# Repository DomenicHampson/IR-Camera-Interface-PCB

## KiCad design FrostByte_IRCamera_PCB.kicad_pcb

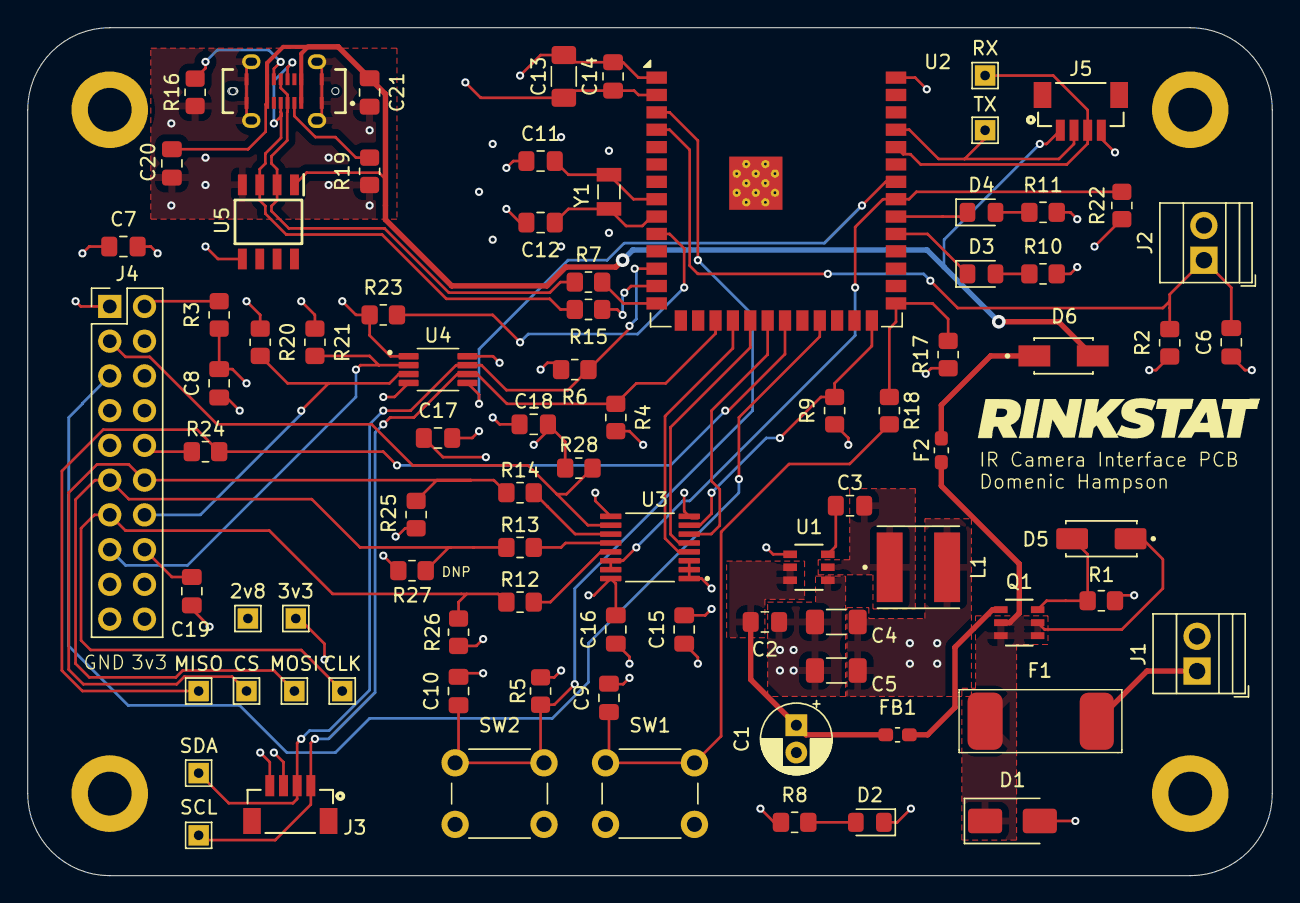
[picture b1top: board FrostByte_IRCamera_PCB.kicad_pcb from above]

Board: 4 copper layers, 91.0 x 62.0 mm, 88 parts (0 on the bottom side), 51 nets.

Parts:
2v8, 3v3: TestPoint; TestPoint_THTPad_1.5x1.5mm_Drill0.7mm
C1: 47uF; CP_Radial_D5.0mm_P2.00mm
C2: 2.2uF; C_0805_2012Metric_Pad1.18x1.45mm_HandSolder
C3, C6, C8, C9, C10, C14, C15, C16, C17, C18, C20, C21: 0.1uF; C_0805_2012Metric_Pad1.18x1.45mm_HandSolder
C4, C5: 22uF; C_1206_3216Metric_Pad1.33x1.80mm_HandSolder
C7, C19: 1uF; C_0805_2012Metric_Pad1.18x1.45mm_HandSolder
C11, C12: 8pF; C_0805_2012Metric_Pad1.18x1.45mm_HandSolder
C13: DNP; C_1206_3216Metric_Pad1.33x1.80mm_HandSolder
CLK: TestPoint; TestPoint_THTPad_1.5x1.5mm_Drill0.7mm
CS: TestPoint; TestPoint_THTPad_1.5x1.5mm_Drill0.7mm
D1: SMAJ33A; D_SMA
D2: LED_Red; LED_0805_2012Metric_Pad1.15x1.40mm_HandSolder
D3: LED_Blue; LED_0805_2012Metric_Pad1.15x1.40mm_HandSolder
D4: LED_Green; LED_0805_2012Metric_Pad1.15x1.40mm_HandSolder
D5: 15V; DIOM5226X240N
D6: B240A-13-F; DIOM5226X230N
F1: 3404.2413.11; Small_SMD_Fuse_Holder
F2: 1A Slow Blow; Fuse_0603_1608Metric_Pad1.05x0.95mm_HandSolder
FB1: PE-0603PFB121ST; C_0603_1608Metric_Pad1.08x0.95mm_HandSolder
H1, H2, H3, H4: MountingHole_Pad; MountingHole_3.2mm_M3_DIN965_Pad
J1: Power_Input; TerminalBlock_Xinya_XY308-2.54-2P_1x02_P2.54mm_Horizontal
J2: Conn_01x02_Socket; TerminalBlock_Xinya_XY308-2.54-2P_1x02_P2.54mm_Horizontal
J3: Conn_01x04_Socket; CONN4_BM04B-SRSS_JST
J4: Conn_02x10; PinHeader_2x10_P2.54mm_Vertical
J5: UART; CONN4_BM04B-SRSS_JST
J6: USB4120-03-C_REVA6; GCT_USB4120-03-C_REVA6
L1: 3.9uH; IND_VLS6045EX-6R8M
MISO: TestPoint; TestPoint_THTPad_1.5x1.5mm_Drill0.7mm
MOSI: TestPoint; TestPoint_THTPad_1.5x1.5mm_Drill0.7mm
Q1: SI3127DV-T1-GE3; TSOP-6L_VIS
R1: 100k; R_0805_2012Metric_Pad1.20x1.40mm_HandSolder
R2: 10k 1%; R_0805_2012Metric_Pad1.20x1.40mm_HandSolder
R3, R5, R9, R17, R22, R23, R25, R28: 10k; R_0805_2012Metric_Pad1.20x1.40mm_HandSolder
R4, R6, R20, R21: 2.2k; R_0805_2012Metric_Pad1.20x1.40mm_HandSolder
R7, R12, R13, R15, R24: 22; R_0805_2012Metric_Pad1.20x1.40mm_HandSolder
R8: 270; R_0805_2012Metric_Pad1.20x1.40mm_HandSolder
R10: 47; R_0805_2012Metric_Pad1.20x1.40mm_HandSolder
R11: 150; R_0805_2012Metric_Pad1.20x1.40mm_HandSolder
R14: 33; R_0805_2012Metric_Pad1.20x1.40mm_HandSolder
R16, R19: 5.1k; R_0805_2012Metric_Pad1.20x1.40mm_HandSolder
R18: 0; R_0805_2012Metric_Pad1.20x1.40mm_HandSolder
R26, R27: 47k; R_0805_2012Metric_Pad1.20x1.40mm_HandSolder
RX: TestPoint; TestPoint_THTPad_1.5x1.5mm_Drill0.7mm
SCL: TestPoint; TestPoint_THTPad_1.5x1.5mm_Drill0.7mm
SDA: TestPoint; TestPoint_THTPad_1.5x1.5mm_Drill0.7mm
SW1, SW2: SW_Push; SW_PUSH_6mm
TX: TestPoint; TestPoint_THTPad_1.5x1.5mm_Drill0.7mm
U1: AP63203WU-7; SOT-23-THIN-6_DDC_TEX
U2: ESP32-S3-WROOM-1
U3: SN74AXC4T245PWR; SOP65P640X120-16N
U4: TCA9517DGKR; SOP65P490X110-8N
U5: USB6B1RL; SOIC127P600X175-8N
Y1: 32.768kHz; XTAL_FC-135R_32.7680KA-AG0

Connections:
+2V8: 2v8.1, C8.1, C16.1, C18.2, C19.2, J4.16, R3.2, R20.1, R21.1, R23.2, R25.1, R26.1, R28.2, U3.16 (VCCB), U4.1 (VCCA)
+3.3V: 3v3.1, C4.1, C5.1, C7.1, C13.1, C14.1, C15.1, C17.1, J3.3, J4.20, L1.2, R2.1, R4.1, R5.2, R6.1, R8.1, R9.1, R10.1, R11.1, R17.2, R22.1, U1.1 (FB), U2.2 (3V3), U3.1 (VCCA), U3.2 (1DIR), U3.3 (2DIR), U4.8 (VCCB)
+5V: C20.2, C21.2, D6.A, J5.1, J6.A4 (VBUS_A), J6.A9 (VBUS_A__1), J6.B4 (VBUS_B), J6.B9 (VBUS_B__1), U5.1 (VCC_1)
/MCU/CAM_TEMP: C6.1, J2.1, R2.2, U2.4 (IO4)
/MCU/EN_I2C: U2.34 (IO41), U4.5 (EN)
/MCU/EN_SPI: R22.2, U2.33 (IO40), U3.14 (2~OE), U3.15 (1~OE)
/MCU/LED_1: D3.1 (K), U2.31 (IO38)
/MCU/LED_2: D4.1 (K), U2.32 (IO39)
/MCU/RESET_L: J4.3, R28.1, U3.10 (2B2)
/MCU/RESET_L_3v3: R9.2, U2.26 (IO45), U3.7 (2A2)
/MCU/RX: J5.3, RX.1, U2.36 (RXD0)
/MCU/SCL_A: J3.1, R4.2, SCL.1, U2.17 (IO9), U4.7 (SCLB)
/MCU/SCL_B: J4.14, R20.2, U4.2 (SCLA)
/MCU/SDA_A: J3.2, R6.2, SDA.1, U2.12 (IO8), U4.6 (SDAB)
/MCU/SDA_B: J4.15, R21.2, U4.3 (SDAA)
/MCU/SPI_CLK: CLK.1, J4.13, R12.1, R26.2
/MCU/SPI_CLK_3v3: U2.20 (IO12), U3.6 (2A1)
/MCU/SPI_CS: CS.1, J4.12, R14.1, R25.2
/MCU/SPI_CS_3v3: U2.18 (IO10), U3.4 (1A1)
/MCU/SPI_MISO: MISO.1, R24.2, U2.21 (IO13)
/MCU/SPI_MOSI: J4.11, MOSI.1, R13.1, R27.1
/MCU/SPI_MOSI_3v3: U2.19 (IO11), U3.5 (1A2)
/MCU/TX: J5.2, TX.1, U2.37 (TXD0)
/MCU/VSYNC: J4.5, U2.23 (IO21)
/Peripherals/USB_D+: J6.A6 (D1+), J6.B6 (D2+), R7.1, R7.2, U2.14 (IO20), U5.2 (I/O1_1)
/Peripherals/USB_D-: J6.A7 (D1-), J6.B7 (D2-), R15.1, R15.2, U2.13 (IO19), U5.3 (I/O2_1)
/Power_Circuitry/source: D1.1 (A1), D5.1 (K), F1.2, F2.1, Q1.1, Q1.2, Q1.5, Q1.6
GND: C1.2, C2.2, C4.2, C5.2, C6.2, C7.2, C8.2, C9.1, C10.1, C11.1, C12.1, C13.2, C14.2, C15.2, C16.2, C17.2, C18.1, C19.1, C20.1, C21.1, D1.2 (A2), D2.1 (K), H1.1, H2.1, H3.1, H4.1, J1.2, J2.2, J3.4, J4.1, J4.19, J5.4, J6.A1 (GND_A), J6.A12 (GND_A__1), J6.B1 (GND_B), J6.B12 (GND_B__1), J6.S1 (SHIELD), J6.S2 (SHIELD__1), J6.S3 (SHIELD__2), J6.S4 (SHIELD__3), R1.1, R16.1, R19.2, R27.2, SW1.1, SW2.1, U1.4 (GND), U2.1 (GND), U2.40 (GND), U2.41 (GND), U3.8 (GND-1), U3.9 (GND), U4.4 (GND), U5.4 (GND_1), U5.5 (GND_2)
unnamed: C9.2, R18.2, SW1.2
unnamed: D2.2 (A), R8.2
unnamed: D3.2 (A), R10.2
unnamed: D4.2 (A), R11.2
unnamed: D5.2 (A), Q1.3, R1.2
unnamed: D6.C, F2.2
unnamed: FB1.1, Q1.4
unnamed: F1.1, J1.1
unnamed: J4.2, R3.1
unnamed: J4.10, R24.1
unnamed: J6.A5 (CC1), R19.1
unnamed: J6.B5 (CC2), R16.2
unnamed: C3.1, U1.6 (BST)
unnamed: C1.1, C2.1, FB1.2, U1.2 (EN), U1.3 (VIN)
unnamed: C3.2, L1.1, U1.5 (SW)
unnamed: C10.2, R5.1, SW2.2, U2.3 (EN)
unnamed: R17.1, R18.1, U2.27 (IO0)
unnamed: C11.2, U2.8 (IO15), Y1.2
unnamed: C12.2, U2.9 (IO16), Y1.1
unnamed: R23.1, U2.10 (IO17)
unnamed: R12.2, U3.13 (1B1)
unnamed: R13.2, U3.12 (1B2)
unnamed: R14.2, U3.11 (2B1)

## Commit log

2026-01-02 Completed Circuit Rev 1
2026-01-03 Schematic + Layout Review Ready First Rev
2026-01-07 rev 2 added usb prog and i2c level shifting
2026-01-10 minor fixes and updated PCB layout
2026-01-21 Updated Schematic and fixed some routing issues
2026-01-31 Layout + Schem complete, rough routing
2026-02-06 Rev A PCB Ordered
